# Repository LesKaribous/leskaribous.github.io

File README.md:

# Les Karibous – Site Web Officiel

## Présentation

**Les Karibous** est une équipe française de robotique fondée en 2011.  
L’objectif de l’équipe est de montrer que la robotique peut être simple et fun à réaliser.

Depuis sa création, Les Karibous participent chaque année à la **Coupe de France de Robotique** (organisée par l’association Planète Sciences), ainsi qu’à la compétition **MakerFight**.  
Cette approche axée sur le plaisir et la simplicité se reflète dans leurs projets et leurs résultats en compétitions.

## Contenu du dépôt

Ce dépôt GitHub contient le **code source du site web officiel** des Karibous.  
Il s’agit d’un site statique généré avec **Jekyll** (thème **Chirpy**) pour présenter l’équipe, ses robots, ses sponsors, et partager des actualités via des articles de blog.

Le dépôt contient notamment :

- Les articles de blog dans le dossier `_posts`
- Les fiches des **robots** dans `_robots`
- Les **sponsors** dans `_sponsors`
- Une **galerie média** dans `_galleries`
- Les fichiers de configuration nécessaires au site

Le site est automatiquement déployé grâce à **GitHub Pages** à l’adresse suivante :  
👉 [https://leskaribous.fr](https://leskaribous.fr)

## Visualisation en local

Pour tester le site localement :

1. **Pré-requis :**  
   Ruby, Bundler et Jekyll doivent être installés sur votre machine.

2. **Installation des dépendances :**
   ```bash
   bundle install

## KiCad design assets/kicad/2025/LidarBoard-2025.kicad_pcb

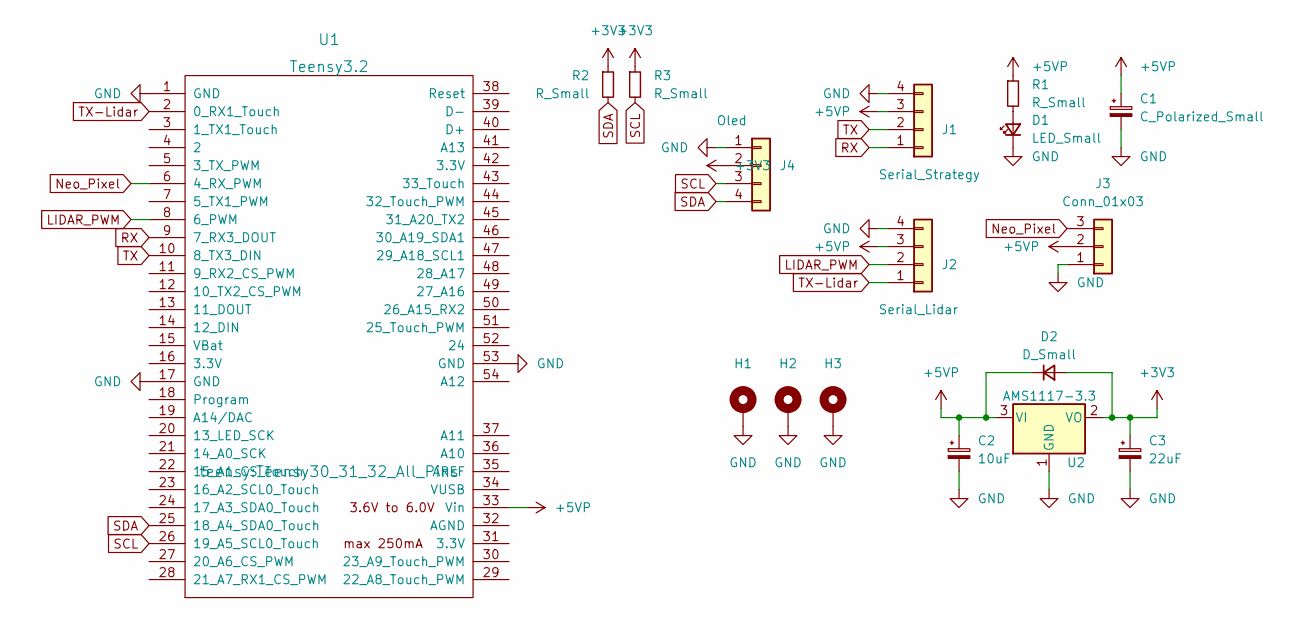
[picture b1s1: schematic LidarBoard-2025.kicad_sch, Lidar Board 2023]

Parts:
C1: C_Polarized_Small; CP_Radial_D6.3mm_P2.50mm
C2: 10uF; CP_Elec_5x5.4
C3: 22uF; CP_EIA-3528-12_Kemet-T_Pad1.50x2.35mm_HandSolder
D1: LED_Small; LED_1206_3216Metric_Pad1.42x1.75mm_HandSolder
D2: D_Small; D_SMA_Handsoldering
H1, H2, H3: MountingHole_Pad; MountingHole_3.2mm_M3_Pad_Via
J1: Serial_Strategy; Molex_KK-254_AE-6410-04A_1x04_P2.54mm_Vertical
J2: Serial_Lidar; Molex_KK-254_AE-6410-04A_1x04_P2.54mm_Vertical
J3: Conn_01x03; Molex_KK-254_AE-6410-03A_1x03_P2.54mm_Vertical
J4: Oled; Molex_KK-254_AE-6410-04A_1x04_P2.54mm_Vertical
R1, R2, R3: R_Small; R_1206_3216Metric_Pad1.30x1.75mm_HandSolder
U1: Teensy3.2; Teensy30_31_32_All_Pins
U2: AMS1117-3.3; SOT-223-3_TabPin2

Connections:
+3V3: C3.1, D2.2 (A), J4.2, R2.1, R3.1, U2.2 (VO)
+5VP: C1.1, C2.1, D2.1 (K), J1.3, J2.3, J3.2, R1.1, U1.33 (Vin), U2.3 (VI)
GND: C1.2, C2.2, C3.2, D1.1 (K), H1.1, H2.1, H3.1, J1.4, J2.4, J3.1, J4.1, U1.1 (GND), U1.17 (GND), U1.53 (GND), U2.1 (GND)
LIDAR_PWM: J2.2, U1.8 (6_PWM)
Neo_Pixel: J3.3, U1.6 (4_RX_PWM)
unnamed: D1.2 (A), R1.2
RX: J1.1, U1.9 (7_RX3_DOUT)
SCL: J4.3, R3.2, U1.26 (19_A5_SCL0_Touch)
SDA: J4.4, R2.2, U1.25 (18_A4_SDA0_Touch)
TX: J1.2, U1.10 (8_TX3_DIN)
TX-Lidar: J2.1, U1.2 (0_RX1_Touch)

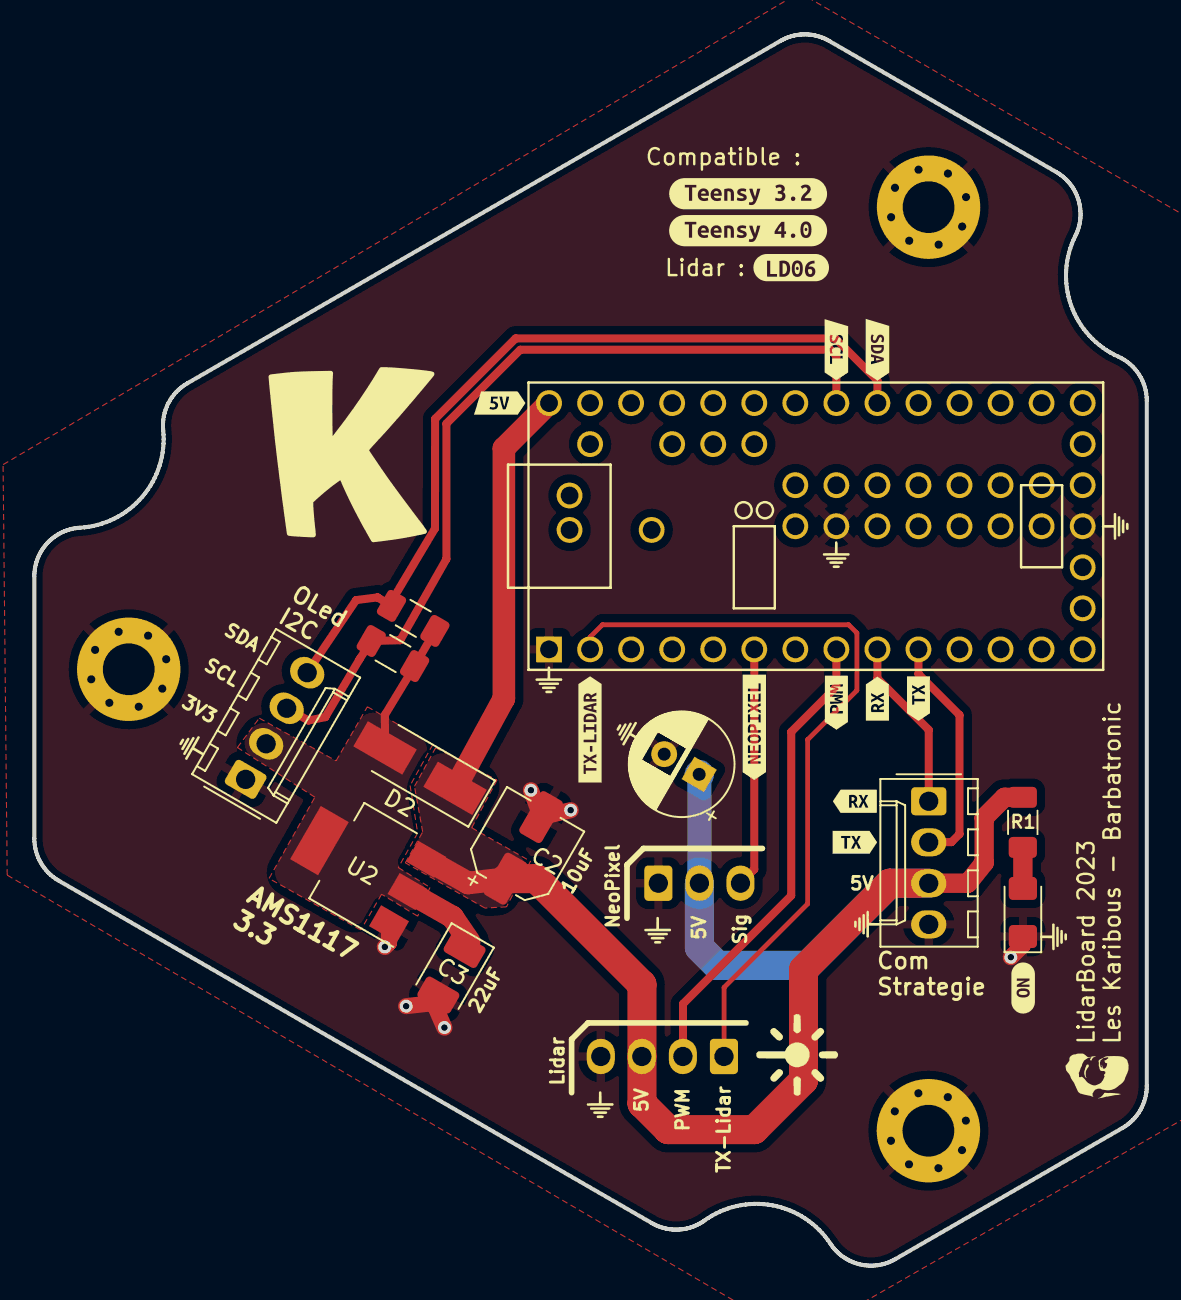
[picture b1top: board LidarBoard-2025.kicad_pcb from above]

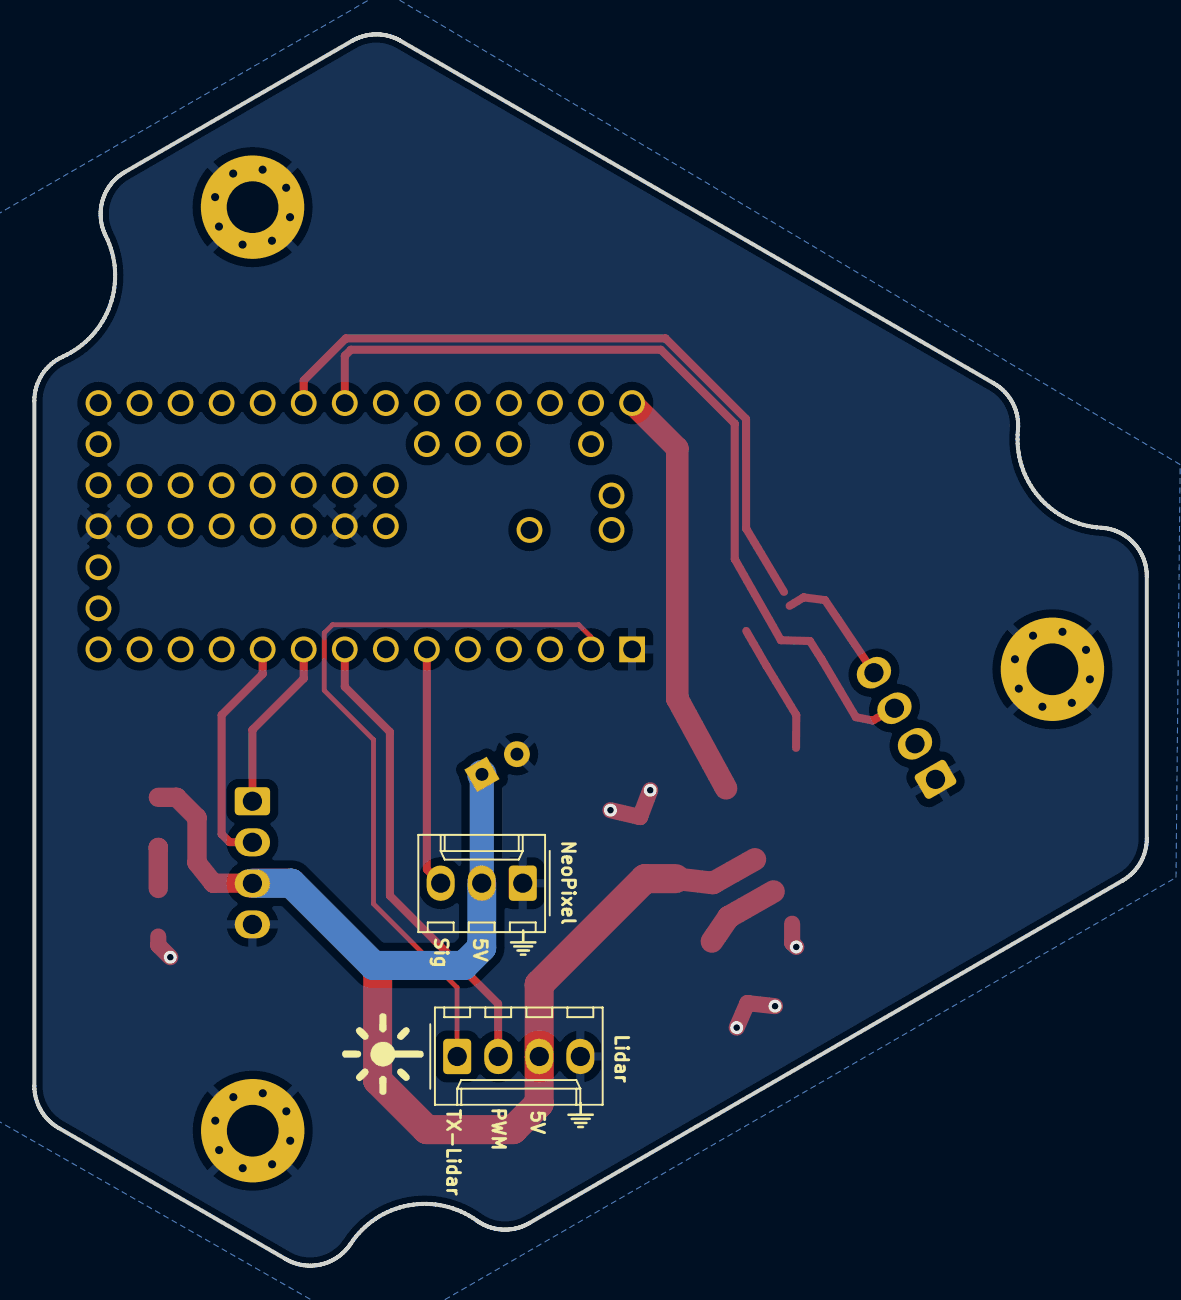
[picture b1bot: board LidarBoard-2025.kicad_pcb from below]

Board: 2 copper layers, 68.8 x 76.2 mm, 31 parts (2 on the bottom side), 11 nets.

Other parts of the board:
kibuzzard-62EFEF5E: G***; kibuzzard-62EFEF5E
kibuzzard-62EFEF6E: G***; kibuzzard-62EFEF6E
kibuzzard-62EFEFDE: G***; kibuzzard-62EFEFDE
kibuzzard-62EFF3FC: G***; kibuzzard-62EFF3FC
kibuzzard-62EFF5A1: G***; kibuzzard-62EFF5A1
kibuzzard-62EFF5AD: G***; kibuzzard-62EFF5AD
kibuzzard-62EFF6AD: G***; kibuzzard-62EFF6AD
kibuzzard-62EFF6BC: G***; kibuzzard-62EFF6BC
kibuzzard-62EFF40D: G***; kibuzzard-62EFF40D
kibuzzard-62EFF59A: G***; kibuzzard-62EFF59A
kibuzzard-62EFF433: G***; kibuzzard-62EFF433
kibuzzard-62EFF540: G***; kibuzzard-62EFF540
kibuzzard-62EFF766: G***; kibuzzard-62EFF766
kibuzzard-62EFF774: G***; kibuzzard-62EFF774

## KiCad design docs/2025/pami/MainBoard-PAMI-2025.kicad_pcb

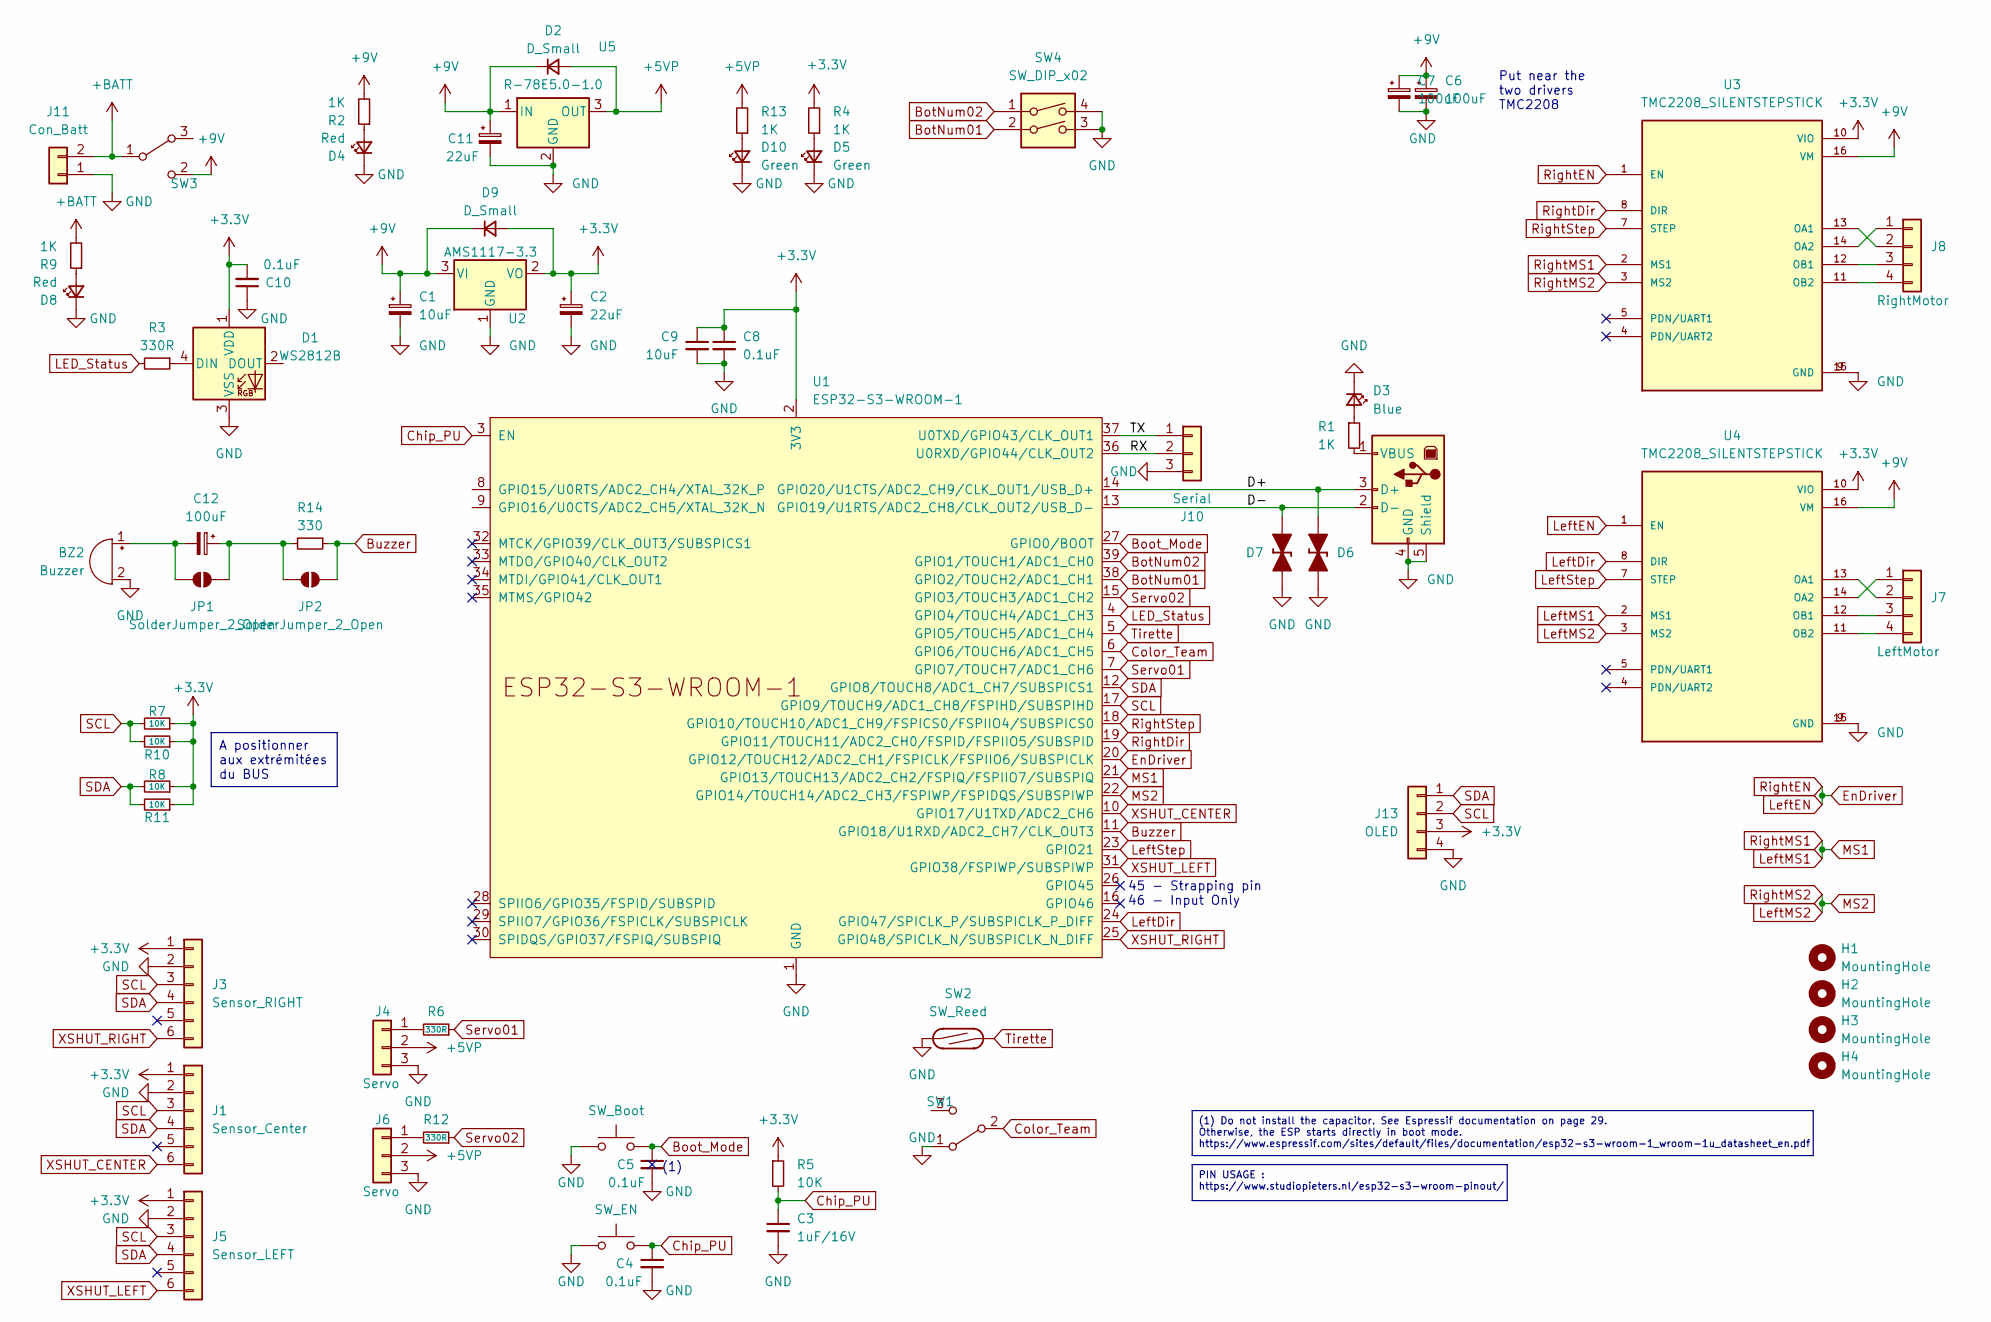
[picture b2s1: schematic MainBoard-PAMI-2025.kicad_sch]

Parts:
BZ2: Buzzer; Buzzer_12x9.5RM7.6
C1: 10uF; CP_Elec_5x5.4
C2: 22uF; CP_EIA-3528-12_Kemet-T_Pad1.50x2.35mm_HandSolder
C3: 1uF/16V; C_1206_3216Metric
C4, C5, C10: 0.1uF; C_1206_3216Metric
C6, C7: 100uF; CP_Radial_D8.0mm_P3.50mm
C8: 0.1uF; C_1206_3216Metric_Pad1.33x1.80mm_HandSolder
C9: 10uF; C_1206_3216Metric_Pad1.33x1.80mm_HandSolder
C11: 22uF; CP_Elec_5x5.4
C12: 100uF; CP_Elec_5x5.4
D1: WS2812B; LED_WS2812B_PLCC4_5.0x5.0mm_P3.2mm
D2, D9: D_Small; D_SMA_Handsoldering
D3: Blue; LED_1206_3216Metric
D4, D8: Red; LED_1206_3216Metric
D5, D10: Green; LED_1206_3216Metric
D6, D7: D_TVS_Bidirectional_Generic; D_SOD-523
H1, H2, H3, H4: MountingHole; MountingHole_3.2mm_M3
J1: Sensor_Center; VL53 Bottom Entry Version
J2: USB_B; USB_B_Lumberg_2411_02_Horizontal
J3: Sensor_RIGHT; VL53 Bottom Entry Version
J4, J6: Servo; PinHeader_1x03_P2.54mm_Vertical
J5: Sensor_LEFT; VL53 Bottom Entry Version
J7: LeftMotor; PinHeader_1x04_P2.54mm_Vertical
J8: RightMotor; PinHeader_1x04_P2.54mm_Vertical
J10: Serial; PinHeader_1x03_P2.54mm_Vertical
J11: Con_Batt; Molex_KK-254_AE-6410-02A_1x02_P2.54mm_Vertical
J13: OLED; PinSocket_1x04_P2.54mm_Vertical
JP1, JP2: SolderJumper_2_Open; SolderJumper-2_P1.3mm_Open_RoundedPad1.0x1.5mm
R1, R2, R4, R9, R13: 1K; R_1206_3216Metric_Pad1.30x1.75mm_HandSolder
R3, R6, R12: 330R; R_1206_3216Metric_Pad1.30x1.75mm_HandSolder
R5, R7, R8, R10, R11: 10K; R_1206_3216Metric_Pad1.30x1.75mm_HandSolder
R14: 330; R_1206_3216Metric_Pad1.30x1.75mm_HandSolder
SW1: SW_SPDT; SK-12D10 1P2T
SW2: SW_Reed; SW_SPST_REED_CT05-XXXX-G1
SW3: SW_SPDT; UB16SKW03N-C
SW4: SW_DIP_x02; SW_DIP_SPSTx02_Slide_9.78x7.26mm_W7.62mm_P2.54mm
SWBoot1: SW_Boot; SW_SPST_CK_RS282G05A3
SWEn1: SW_EN; SW_SPST_CK_RS282G05A3
U1: ESP32-S3-WROOM-1; ESP32-S3-WROOM-1U
U2: AMS1117-3.3; SOT-223-3_TabPin2
U3, U4: TMC2208_SILENTSTEPSTICK; Step-Stick Driver Bottom Entry Version
U5: R-78E5.0-1.0; Converter_DCDC_RECOM_R-78E-0.5_THT

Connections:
+3.3V: C2.1, C8.1, C9.1, C10.2, D1.1 (VDD), D9.2 (A), J1.1, J3.1, J5.1, J13.3, R4.2, R5.1, R7.1, R8.1, R10.1, R11.1, U1.2 (3V3), U2.2 (VO), U3.10 (VIO), U4.10 (VIO); also elsewhere on the board
+5VP: D2.2 (A), J4.2, J6.2, R13.2, U5.3 (OUT)
+9V: C1.1, C6.1, C7.1, C11.1, D2.1 (K), D9.1 (K), R2.2, SW3.2 (C), U2.3 (VI), U3.16 (VM), U4.16 (VM), U5.1 (IN)
+BATT: J11.2, R9.2, SW3.1 (B)
/D+: D6.2 (A), J2.3 (D+), U1.14 (GPIO20/U1CTS/ADC2_CH9/CLK_OUT1/USB_D+)
/D-: D7.2 (A), J2.2 (D-), U1.13 (GPIO19/U1RTS/ADC2_CH8/CLK_OUT2/USB_D-)
/RX: J10.2, U1.36 (U0RXD/GPIO44/CLK_OUT2)
/TX: J10.1, U1.37 (U0TXD/GPIO43/CLK_OUT1)
Boot_Mode: C5.1, SWBoot1.2, U1.27 (GPIO0/BOOT)
BotNum01: SW4.2, U1.38 (GPIO2/TOUCH2/ADC1_CH1)
BotNum02: SW4.1, U1.39 (GPIO1/TOUCH1/ADC1_CH0)
Buzzer: JP2.2 (B), R14.1, U1.11 (GPIO18/U1RXD/ADC2_CH7/CLK_OUT3)
Chip_PU: C3.1, C4.1, R5.2, SWEn1.2, U1.3 (EN)
Color_Team: SW1.2 (B), U1.6 (GPIO6/TOUCH6/ADC1_CH5)
EnDriver: U1.20 (GPIO12/TOUCH12/ADC2_CH1/FSPICLK/FSPIIO6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), U3.1 (EN), U4.1 (EN)
GND: BZ2.2 (-), C1.2, C2.2, C3.2, C4.2, C5.2, C6.2, C7.2, C8.2, C9.2, C10.1, C11.2, D1.3 (VSS), D3.1 (K), D4.1 (K), D5.1 (K), D6.1 (K), D7.1 (K), D8.1 (K), D10.1 (K), H1.1, H2.1, H3.1, H4.1, J1.2, J2.4 (GND), J2.5 (Shield), J3.2, J4.3, J5.2, J6.3, J10.3, J11.1, J13.4, SW1.1 (A), SW4.3, SW4.4, SWBoot1.1, SWEn1.1, U1.1 (GND), U1.40 (GND), U1.41 (GND), U2.1 (GND), U3.9 (GND), U3.15 (GND), U4.9 (GND), U4.15 (GND), U5.2 (GND); also elsewhere on the board
LED_Status: R3.2, U1.4 (GPIO4/TOUCH4/ADC1_CH3)
LeftDir: U1.24 (GPIO47/SPICLK_P/SUBSPICLK_P_DIFF), U4.8 (DIR)
LeftMS1: U1.21 (GPIO13/TOUCH13/ADC2_CH2/FSPIQ/FSPIIO7/S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), U3.2 (MS1), U4.2 (MS1)
LeftMS2: U1.22 (GPIO14/TOUCH14/ADC2_CH3/FSPIWP/FSPIDQS/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), U3.3 (MS2), U4.3 (MS2)
LeftStep: U1.23 (GPIO21), U4.7 (STEP)
unnamed: BZ2.1 (+), C12.2, JP1.1 (A)
unnamed: D1.4 (DIN), R3.1
unnamed: D3.2 (A), R1.1
unnamed: D4.2 (A), R2.1
unnamed: D5.2 (A), R4.1
unnamed: D8.2 (A), R9.1
unnamed: D10.2 (A), R13.1
unnamed: J2.1 (VBUS), R1.2
unnamed: J4.1, R6.2
unnamed: J6.1, R12.2
unnamed: J7.1, U4.14 (OA2)
unnamed: J7.2, U4.13 (OA1)
unnamed: J7.3, U4.12 (OB1)
unnamed: J7.4, U4.11 (OB2)
unnamed: J8.1, U3.14 (OA2)
unnamed: J8.2, U3.13 (OA1)
unnamed: J8.3, U3.12 (OB1)
unnamed: J8.4, U3.11 (OB2)
unnamed: C12.1, JP1.2 (B), JP2.1 (A), R14.2
RightDir: U1.19 (GPIO11/TOUCH11/ADC2_CH0/FSPID/FSPIIO5/S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), U3.8 (DIR)
RightStep: U1.18 (GPIO10/TOUCH10/ADC1_CH9/FSPICS0/FSPIIO4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), U3.7 (STEP)
SCL: J1.3, J3.3, J5.3, J13.2, R7.2, R10.2, U1.17 (GPIO9/TOUCH9/ADC1_CH8/FSPIHD/SUBSPIHD)
SDA: J1.4, J3.4, J5.4, J13.1, R8.2, R11.2, U1.12 (GPIO8/TOUCH8/ADC1_CH7/SUBSPICS1)
Servo01: R6.1, U1.7 (GPIO7/TOUCH7/ADC1_CH6)
Servo02: R12.1, U1.15 (GPIO3/TOUCH3/ADC1_CH2)
Tirette: SW2.2, U1.5 (GPIO5/TOUCH5/ADC1_CH4); also elsewhere on the board
XSHUT_CENTER: J1.6, U1.10 (GPIO17/U1TXD/ADC2_CH6)
XSHUT_LEFT: J5.6, U1.31 (GPIO38/FSPIWP/SUBSPIWP)
XSHUT_RIGHT: J3.6, U1.25 (GPIO48/SPICLK_N/SUBSPICLK_N_DIFF)

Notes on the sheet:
PIN USAGE : https://www.studiopieters.nl/esp32-s3-wroom-pinout/
A positionner aux extrémitées du BUS
(1) Do not install the capacitor. See Espressif documentation on page 29. Otherwise, the ESP starts directly in boot mode. https://www.espressif.com/sites/default/files/documentation/esp32-s3-wroom-1_wroom-1u_datasheet_en.pdf
Put near the two drivers TMC2208
(1)
45 - Strapping pin 46 - Input Only

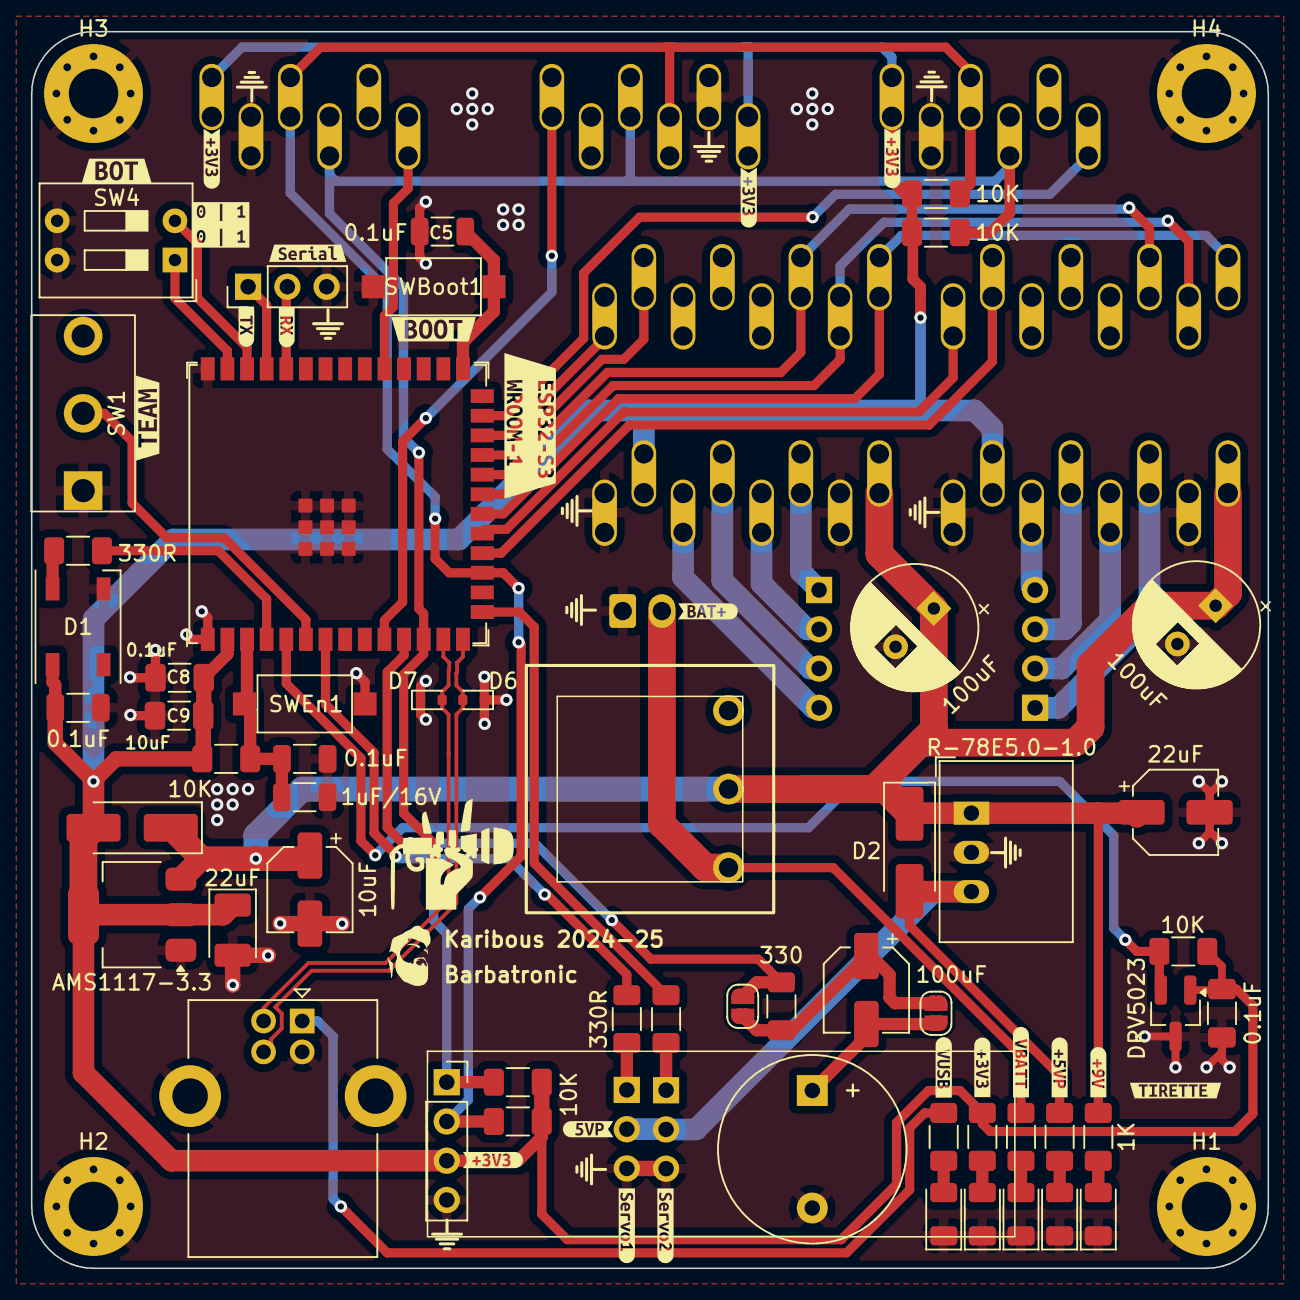
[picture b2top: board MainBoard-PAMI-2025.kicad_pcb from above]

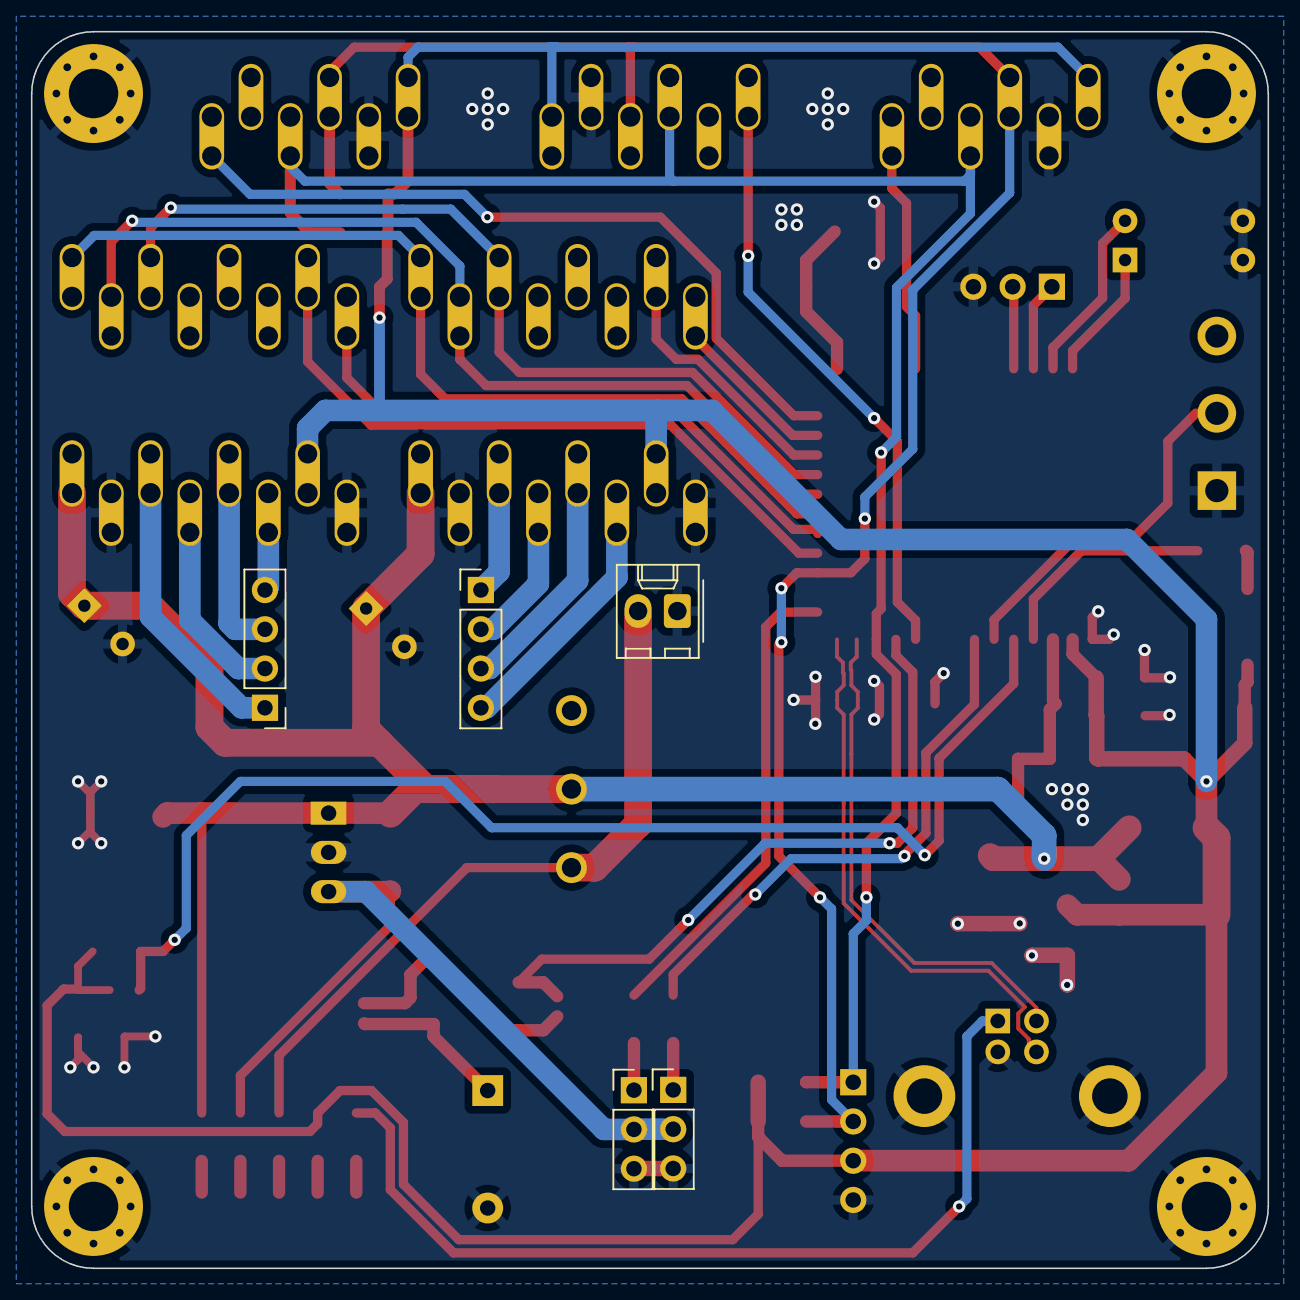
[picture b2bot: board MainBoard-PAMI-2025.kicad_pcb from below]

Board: 2 copper layers, 80.0 x 80.0 mm, 89 parts (8 on the bottom side), 50 nets.

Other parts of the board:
C13: 0.1uF; C_1206_3216Metric_Pad1.33x1.80mm_HandSolder
R15: 10K; R_1206_3216Metric_Pad1.30x1.75mm_HandSolder
U6: DRV5023; SOT-23_Handsoldering
kibuzzard-670C04A5, kibuzzard-670C04A5#2, kibuzzard-670C04A5#3, kibuzzard-670C04A5#4: G***; kibuzzard-670C04A5
kibuzzard-670C04EF: G***; kibuzzard-670C04EF
kibuzzard-670C05E9: G***; kibuzzard-670C05E9
kibuzzard-670C07A3: G***; kibuzzard-670C07A3
kibuzzard-670C07E1: G***; kibuzzard-670C07E1
kibuzzard-670C23C9: G***; kibuzzard-670C23C9
kibuzzard-670C045B: G***; kibuzzard-670C045B
kibuzzard-670C047F: G***; kibuzzard-670C047F
kibuzzard-670C057C: G***; kibuzzard-670C057C
kibuzzard-670C058F: G***; kibuzzard-670C058F
kibuzzard-670C060B: G***; kibuzzard-670C060B
kibuzzard-670C061D: G***; kibuzzard-670C061D
kibuzzard-670C077D: G***; kibuzzard-670C077D
kibuzzard-670C0418: G***; kibuzzard-670C0418
kibuzzard-670C0436: G***; kibuzzard-670C0436
kibuzzard-670C0507: G***; kibuzzard-670C0507
kibuzzard-670C0614: G***; kibuzzard-670C0614
kibuzzard-670C0624: G***; kibuzzard-670C0624
kibuzzard-670C0798: G***; kibuzzard-670C0798

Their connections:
+3.3V: C13.1, R15.2, U6.1 (VCC); also elsewhere on the board
GND: C13.2, U6.3 (GND); also elsewhere on the board
Tirette: R15.1, U6.2 (OUT); also elsewhere on the board

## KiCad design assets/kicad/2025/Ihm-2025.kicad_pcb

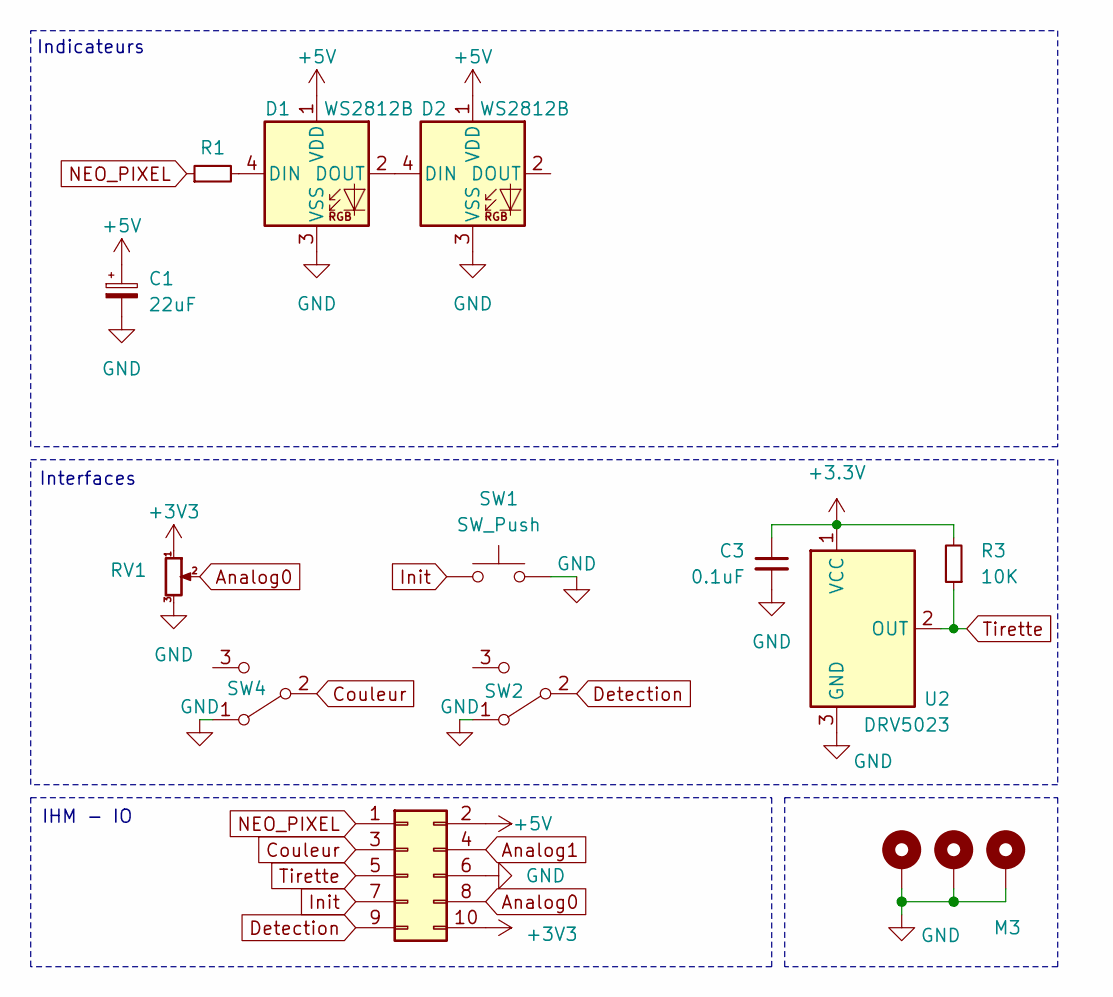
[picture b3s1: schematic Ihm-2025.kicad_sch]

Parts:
C1: 22uF; CP_Elec_5x5.4
C3: 0.1uF; C_1206_3216Metric_Pad1.33x1.80mm_HandSolder
D1, D2: WS2812B; LED_WS2812B_PLCC4_5.0x5.0mm_P3.2mm
H2, H3, H4: M3; MountingHole_3.2mm_M3_Pad_Via
IHM-IO1: Conn_02x05_Odd_Even; IDC-Header_2x05_P2.54mm_Vertical
R1: R_Small; R_1206_3216Metric_Pad1.30x1.75mm_HandSolder
R3: 10K; R_1206_3216Metric_Pad1.30x1.75mm_HandSolder
RV1: R_Potentiometer_Small; Potentiometer_Bourns_PTV09A-1_Single_Vertical
SW1: SW_Push; SW_Cherry_MX_PCB_1.00u
SW2, SW4: SW_SPDT; SK-12D10 1P2T
U2: DRV5023; SOT-23_Handsoldering

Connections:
+3.3V: C3.1, R3.2, U2.1 (VCC)
+3V3: IHM-IO1.10, RV1.1
+5V: C1.1, D1.1 (VDD), D2.1 (VDD), IHM-IO1.2
Analog0: IHM-IO1.8, RV1.2
Analog1: IHM-IO1.4
Couleur: IHM-IO1.3, SW4.2 (B)
Detection: IHM-IO1.9, SW2.2 (B)
GND: C1.2, C3.2, D1.3 (VSS), D2.3 (VSS), H2.1, H3.1, H4.1, IHM-IO1.6, RV1.3, SW1.2, SW2.1 (A), SW4.1 (A), U2.3 (GND)
Init: IHM-IO1.7, SW1.1
NEO_PIXEL: IHM-IO1.1, R1.1
unnamed: D1.4 (DIN), R1.2
unnamed: D1.2 (DOUT), D2.4 (DIN)
Tirette: IHM-IO1.5, R3.1, U2.2 (OUT)

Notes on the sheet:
Interfaces
IHM - IO
Indicateurs

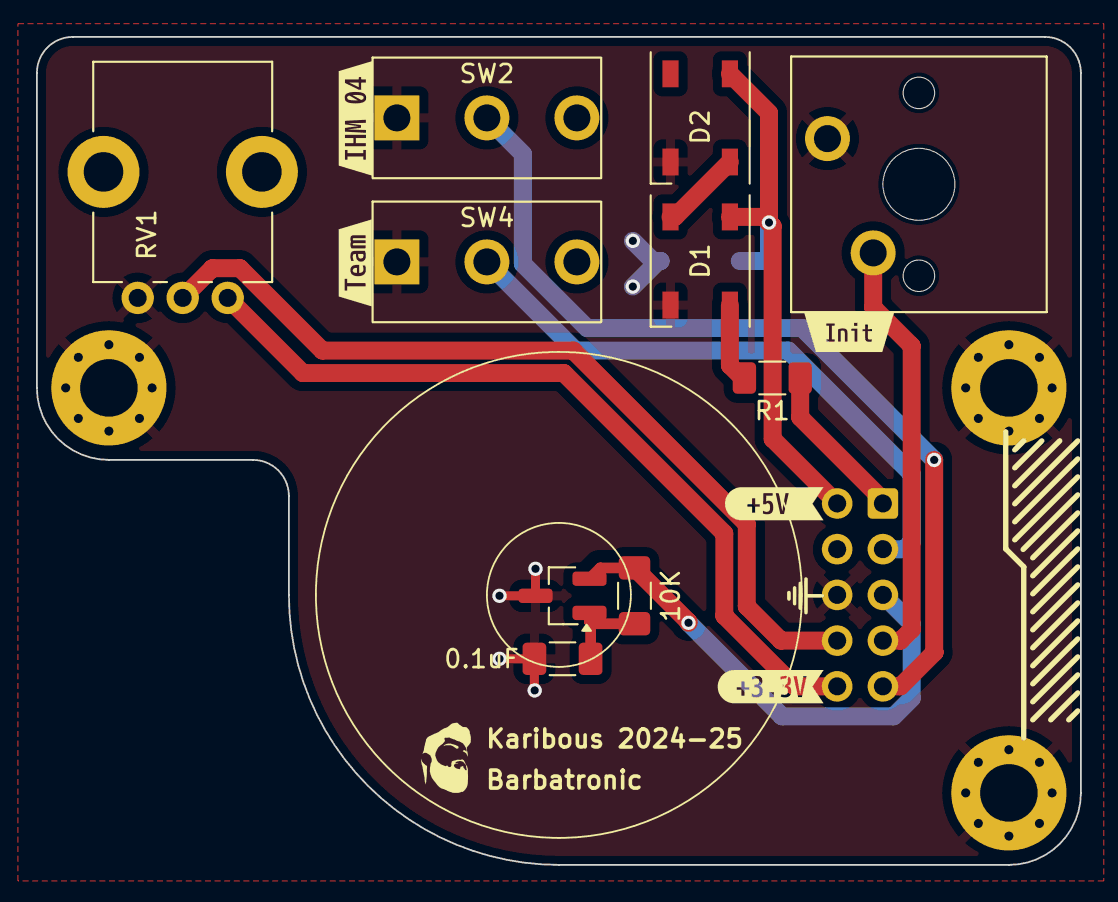
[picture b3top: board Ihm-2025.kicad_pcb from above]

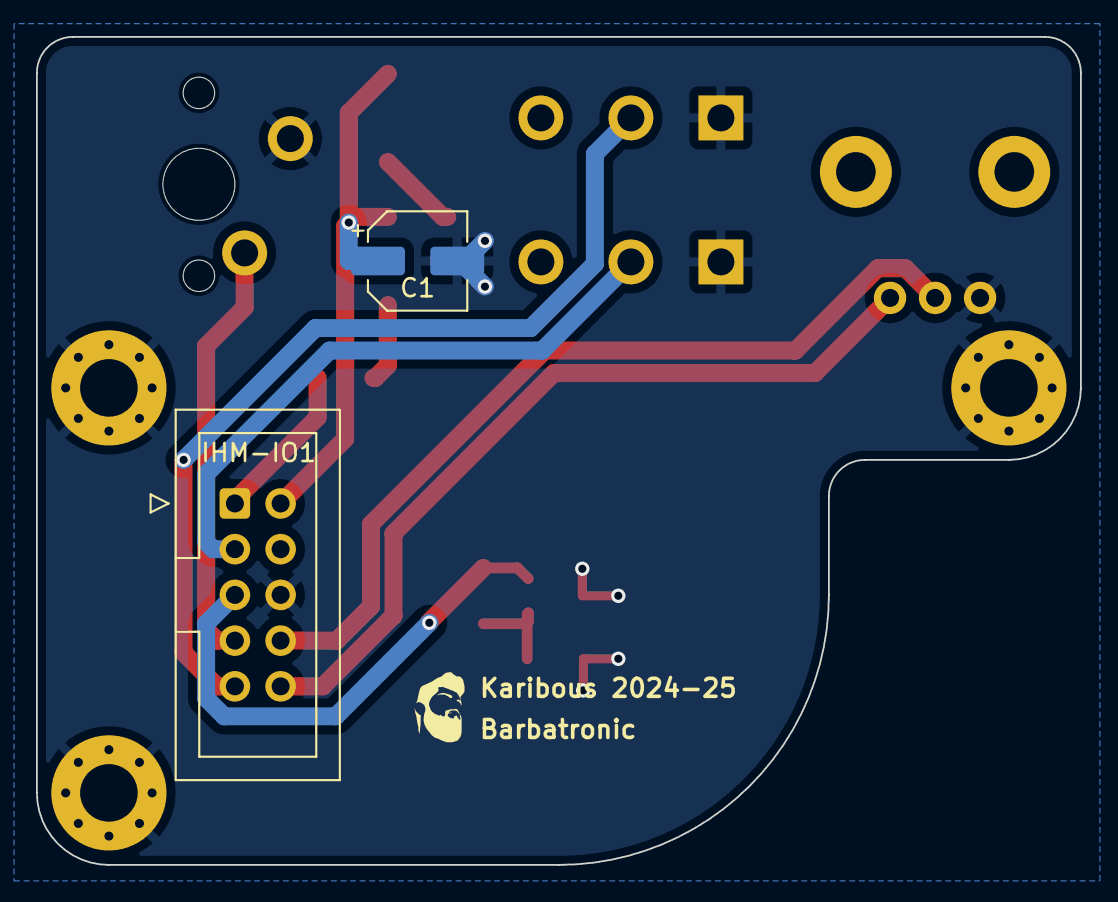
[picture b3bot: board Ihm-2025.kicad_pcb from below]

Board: 2 copper layers, 58.0 x 46.0 mm, 20 parts (2 on the bottom side), 12 nets.

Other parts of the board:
kibuzzard-64A1DF46: G***; kibuzzard-64A1DF46
kibuzzard-64A1DF73: G***; kibuzzard-64A1DF73
kibuzzard-64A1DFA1: G***; kibuzzard-64A1DFA1
kibuzzard-64A1DFD6: G***; kibuzzard-64A1DFD6
kibuzzard-666F551A: G***; kibuzzard-666F551A
